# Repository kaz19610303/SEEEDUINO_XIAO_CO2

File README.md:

# SEEEDUINO_XIAO_CO2
CO2 monitor board using SEEEDUINO XIAO

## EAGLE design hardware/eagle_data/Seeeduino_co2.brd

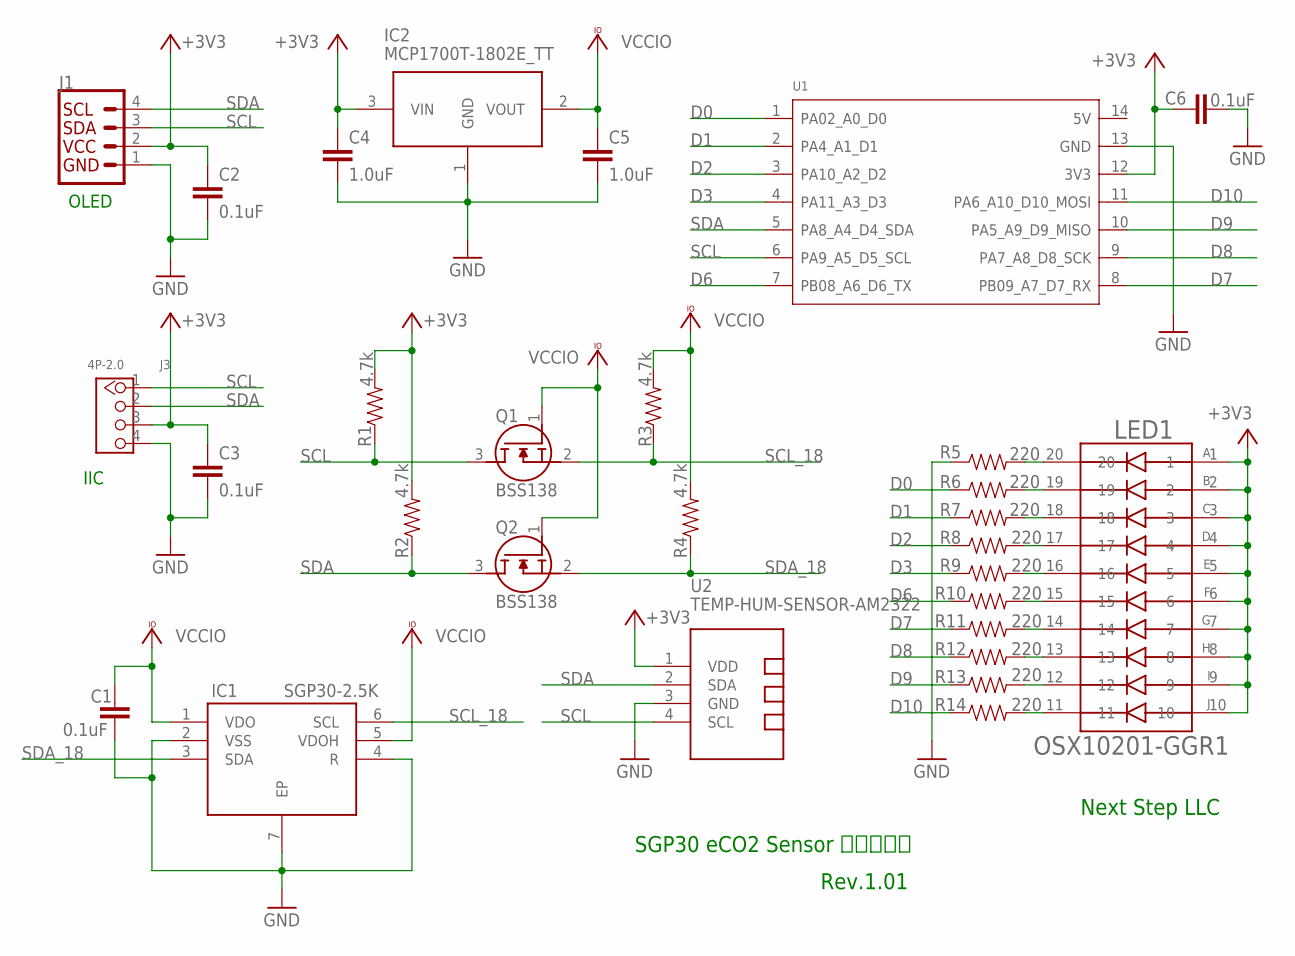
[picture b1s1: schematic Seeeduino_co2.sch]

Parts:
C1, C2, C3, C6: 0.1uF; 0402
C4, C5: 1.0uF; 0402
IC1: SGP30-2.5K; SON80P245X245X90-7N
IC2: MCP1700T-1802E_TT; SOT95P237X112-3N
J1: I2C_STANDARD; 1X04
J3: 4P-2.0; HW4-2.0
LED1: OSX10201-GGR1; DIP760W45P254L2550H790Q20
Q1, Q2: BSS138; SOT95P240X120-3N
R1, R2, R3, R4: 4.7k; 0603
R5, R6, R7, R8, R9, R10, R11, R12, R13, R14: 220; 0603
U1: MOUDLE-SEEEDUINO-XIAO; MOUDLE14P-2.54-21X17.8MM
U2: TEMP-HUM-SENSOR-AM2322

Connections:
+3V3: C2.1, C3.1, C4.1, C6.1, IC2.3 (VIN), J1.2, J3.3, LED1.1, LED1.2, LED1.3, LED1.4, LED1.5, LED1.6, LED1.7, LED1.8, LED1.9, LED1.10, R1.2, R2.2, U1.12 (3V3), U2.1 (VDD)
D0: R6.1, U1.1 (PA02_A0_D0)
D1: R7.1, U1.2 (PA4_A1_D1)
D2: R8.1, U1.3 (PA10_A2_D2)
D3: R9.1, U1.4 (PA11_A3_D3)
D6: R10.1, U1.7 (PB08_A6_D6_TX)
D7: R11.1, U1.8 (PB09_A7_D7_RX)
D8: R12.1, U1.9 (PA7_A8_D8_SCK)
D9: R13.1, U1.10 (PA5_A9_D9_MISO)
D10: R14.1, U1.11 (PA6_A10_D10_MOSI)
GND: C1.2, C2.2, C3.2, C4.2, C5.2, C6.2, IC1.2 (VSS), IC1.4 (R), IC1.7 (EP), IC2.1 (GND), J1.1, J3.4, R5.1, U1.13 (GND), U2.3 (GND)
unnamed: LED1.11, R14.2
unnamed: LED1.12, R13.2
unnamed: LED1.13, R12.2
unnamed: LED1.14, R11.2
unnamed: LED1.15, R10.2
unnamed: LED1.16, R9.2
unnamed: LED1.17, R8.2
unnamed: LED1.18, R7.2
unnamed: LED1.19, R6.2
unnamed: LED1.20, R5.2
SCL: J1.3, J3.1, Q1.3 (D), R1.1, U1.6 (PA9_A5_D5_SCL), U2.4 (SCL)
SCL_18: IC1.6 (SCL), Q1.2 (S), R3.1
SDA: J1.4, J3.2, Q2.3 (D), R2.1, U1.5 (PA8_A4_D4_SDA), U2.2 (SDA)
SDA_18: IC1.3 (SDA), Q2.2 (S), R4.1
VCCIO: C1.1, C5.1, IC1.1 (VDO), IC1.5 (VDOH), IC2.2 (VOUT), Q1.1 (G), Q2.1 (G), R3.2, R4.2

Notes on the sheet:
OLED
IIC
SGP30 eCO2 Sensor ｂｏａｒｄ
Next Step LLC
Rev.1.01

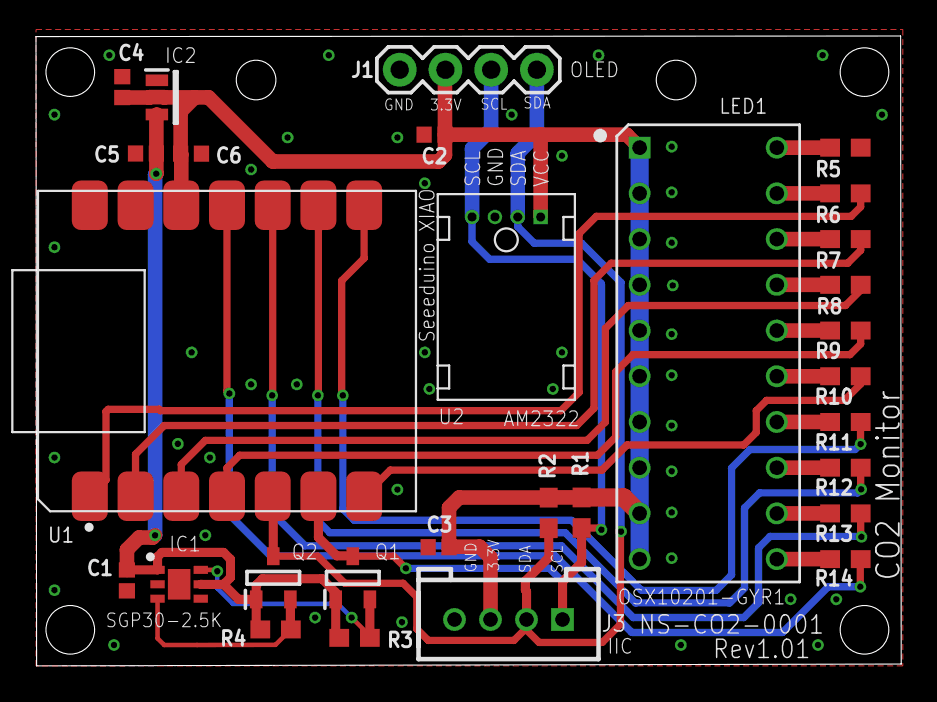
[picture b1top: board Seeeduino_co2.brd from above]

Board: 2 copper layers, 48.1 x 35.0 mm, 29 parts (0 on the bottom side), 26 nets.

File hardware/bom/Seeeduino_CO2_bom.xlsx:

Parts | Qty | LEDアレイ版バン | OLED版バン | OLED版(温度付き)オンドツ | Value | Device | Package | Description
C1, C2, C3, C6 | 4 |  |  |  | 0.1uF | 0.1uF-0402-16V-10% | 0402 | 0.1uF ceramic capacitors
C4, C5 | 2 |  |  |  | 1.0uF | 1.0uF-0402-16V-10% | 0402 | 1uF ceramic capacitors
IC1 | 1 |  |  |  | SGP30-2.5K | SGP30-2.5K | SON80P245X245X90-7N | Air Quality Sensors Multi-Pixel SGP Gas Sensor
IC2 | 1 |  |  |  | MCP1700T-1802E_TT | MCP1700T-1802E_TT | SOT95P237X112-3N | Microchip MCP1700T-1802E/TT, LDO Voltage Regulator, 200mA, 1.8 V +/-2%, 2.3 6 V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
J1 | 1 | × |  |  |  | I2C_STANDARD | 1X04 | SparkFun I2C Standard Pinout Header
J3 | 1 | × | × | × | 4P-2.0 | GROVE-CONNECTOR-DIP(4P-2.0) | HW4-2.0 | 320110033
LED1 | 1 |  | × | × | OSX10201-GGR1 | OSX10201-GGR1 | DIP760W45P254L2550H790Q20 | Display: LED; bargraph; green (7x) / red (3x); 25.5x10.2x7.9mm
Q1, Q2 | 2 |  |  |  | BSS138 | BSS138 | SOT95P240X120-3N | N-channel MOSFET,BSS138 0.2A 50V
R1, R2, R3, R4 | 4 |  |  |  | 4.7k | 4.7kOHM-0603-1/10W-1% | 0603 | 4.7kΩ resistor
R5, R6, R7, R8, R9, R10, R11, R12, R13, R14 | 10 |  | × | × | 220 | 220OHM-0603-1/10W-1% | 0603 | 220Ω resistor
U1 | 1 |  |  |  |  | MOUDLE-SEEEDUINO-XIAO | MOUDLE14P-2.54-21X17.8MM
U2 | 1 | × | × |  | TEMP-HUM-SENSOR-AM2322 | TEMP-HUM-SENSOR-AM2322 | TEMP-HUM-SENSOR-AM2322 | AM2322 - digital humidity & temperature sensor
OLED1 | 1 | × |  |  |  |  |  | 0.96インチ 128×64ドット有機ELディスプレイ

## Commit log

2021-01-20 First commit.

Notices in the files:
parts and their libraries:
SparkFun-Resistors: Licensing: Creative Commons ShareAlike 4.0 International - https://creativecommons.org/licenses/by-sa/4.0
diy-modules: Released under the Creative Commons Attribution 4.0 International License: http://creativecommons.org/licenses/by/4.0
